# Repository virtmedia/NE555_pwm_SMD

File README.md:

# NE555_pwm_SMD
Simple, small and cheap PWM regulator on NE555.

Single-sided pcb layout with only 1 jumper.

You can use it to drive 12V motor, LED strip, Peltier module, lightbulb etc.
PCB dimensions: 34.29 x 20.63 mm. 
Pulse width regulated by standard potentiometer.
You can use any Mosfet in DPAK (TO-252) case as You like and follow Your requirements. I am using 2SK3918 from old pc motherboard.

I also designed even smaller version with components on both sides, but is now without tests. 

As soon as possible i make photos and movie to show prototype.

If You want to make it, just download the ne555_pwm_smd_top.pdf file, print it and make thermotransfer.
All SMD resistors and capacitors are in 1206 cases.
You can find partlist in bom.txt file.

Schematic:

PCB layout:

Partlist (from file bom.txt):
Part Value  Device         Package   Description                  
C1   100n   C-EUC1206      C1206     CAPACITOR, European symbol   
C2   100n   C-EUC1206      C1206     CAPACITOR, European symbol   
C3   10n    C-EUC1206      C1206     CAPACITOR, European symbol   
D1   LL4148 DIODE-MINIMELF MINIMELF  DIODE                        
D2   LL4148 DIODE-MINIMELF MINIMELF  DIODE                        
D3   LL4148 DIODE-MINIMELF MINIMELF  DIODE                        
IC1  NE555D NE555D         SO08      TIMER                        
JP1  ZAS    PINHD-1X2      1X02      PIN HEADER                   
JP2  OUT    PINHD-1X2      1X02      PIN HEADER                   
Q1   MFET-N 	TO252_STM  TO252_STM IGBT                         
R1   1K     R-EU_R1206     R1206     RESISTOR, European symbol    
R2   47R    R-EU_R1206     R1206     RESISTOR, European symbol    
R3   100K   3RP/1610N      3RP/1610N 16mm Potentiometer one level

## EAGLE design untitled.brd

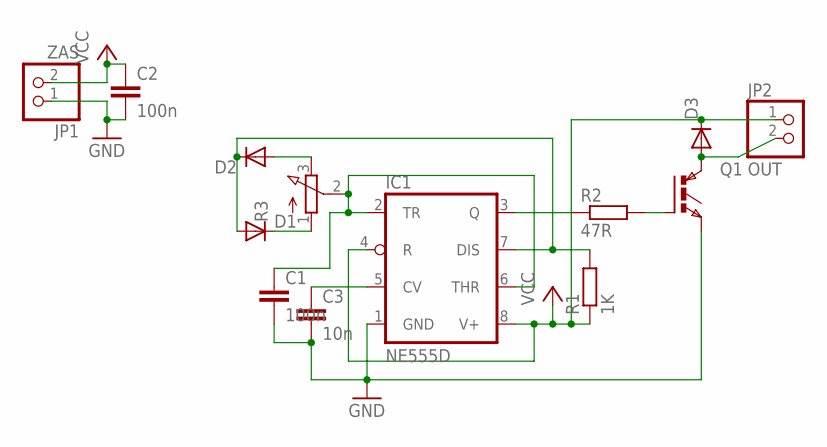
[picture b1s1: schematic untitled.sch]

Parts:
C1, C2: 100n; C1206
C3: 10n; C1206
D1, D2, D3: DIODE-MINIMELF; MINIMELF
IC1: NE555D; SO08
JP1: ZAS; 1X02
JP2: OUT; 1X02
Q1: IGBTTO252_STM; TO252_STM
R1: 1K; R1206
R2: 47R; R1206
R3: 3RP/1610N

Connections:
GND: C1.2, C2.2, C3.2, IC1.1 (GND), JP1.1, Q1.3 (E)
unnamed: C1.1, IC1.2 (TR), IC1.6 (THR), R3.2 (S)
unnamed: D1.C, R3.1 (A)
unnamed: D2.A, R3.3 (E)
unnamed: D1.A, D2.C, IC1.7 (DIS), R1.2
unnamed: IC1.3 (Q), R2.1
unnamed: Q1.1 (G), R2.2
unnamed: C3.1, IC1.5 (CV)
unnamed: D3.A, JP2.2, Q1.2 (C)
VCC: C2.1, D3.C, IC1.4 (R), IC1.8 (V+), JP1.2, JP2.1, R1.1

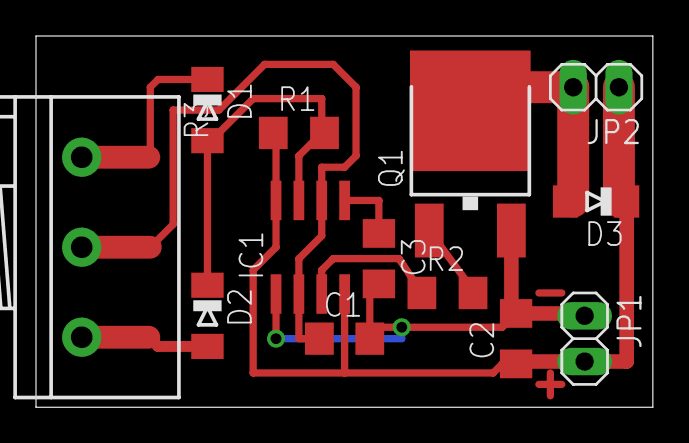
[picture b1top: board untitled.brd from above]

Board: 2 copper layers, 34.3 x 20.6 mm, 13 parts (0 on the bottom side), 10 nets.

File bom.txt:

Partlist exported from J:/elektronika/Projekty/Wlasne/Eagle/Wykonane/NE555_pwm_SMD/untitled.sch at 2015-09-28 11:50:41

Part Value  Device         Package   Description                  
C1   100n   C-EUC1206      C1206     CAPACITOR, European symbol   
C2   100n   C-EUC1206      C1206     CAPACITOR, European symbol   
C3   10n    C-EUC1206      C1206     CAPACITOR, European symbol   
D1          DIODE-MINIMELF MINIMELF  DIODE                        
D2          DIODE-MINIMELF MINIMELF  DIODE                        
D3          DIODE-MINIMELF MINIMELF  DIODE                        
IC1  NE555D NE555D         SO08      TIMER                        
JP1  ZAS    PINHD-1X2      1X02      PIN HEADER                   
JP2  OUT    PINHD-1X2      1X02      PIN HEADER                   
Q1          IGBTTO252_STM  TO252_STM IGBT                         
R1   1K     R-EU_R1206     R1206     RESISTOR, European symbol    
R2   47R    R-EU_R1206     R1206     RESISTOR, European symbol    
R3          3RP/1610N      3RP/1610N 16mm Potentiometer one level

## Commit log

2015-09-28 :confetti_ball: Added .gitattributes & .gitignore files
2015-09-28 Images added.
2015-09-28 fixed git.ignore
2015-09-28 fixed gitignore
2018-07-07 added photo of the device
